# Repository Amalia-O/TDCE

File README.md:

# TDCE
FIUBA - Electrónica - Taller de Diseño de Circuitos Electrónicos - Trabajo Integrador

idealmente : RD2 = 1093 ohm RC1 RC2 deben ser iguales entre entre {100 y 1k} ohm. Admiten una dispersion de 10%. RE = 1.5k, A RC iguales tiende a desequilibrar el circuito cuando aumenta en valor. Es preferible que RE sea menor en vez de mayor. A RC2 > RC1 : punto de reposo en 4.97 y siguie siendo mejor que RE sea mejor a que sea mayor A RC1 > RC2 : Punto de reposo en 5v! conviene mucho mas que RE sea mas chica

Eficiencia:
  75.5 - 71.2 : En Re = 1.5k y par diferencial no darlington. Regulacion de linea es -2e-5. Regulacion de carga es 4e-5. Corriente por Re 0.65 mA.En este caso hay mayor RRMC que con RE= 1k.
  75.5 - 71.2 : En Re = 1.0k y par diferencial no darlington. Regulacion de linea es -2e-5. Regulacion de carga es 4e-5. Corriente por Re \simeq 1mA. Ganancia de lazo 80dB. lazo cerrado es de 98dB
  75.5 - 71.2 : En Re = 1.5K y par diferencial darlington. Regulacion de linea es de 9e-5. Regulacion de carga es 0.0002. Corriente por Re \simeq 0.4mA
  75.4 - 71.4 : En Re = 500 y par diferencial darlington. Regulacion de linea es 2.75e-5. Regulacion de carga es 9.95e-5. Corriente por Re \simeq 1mA

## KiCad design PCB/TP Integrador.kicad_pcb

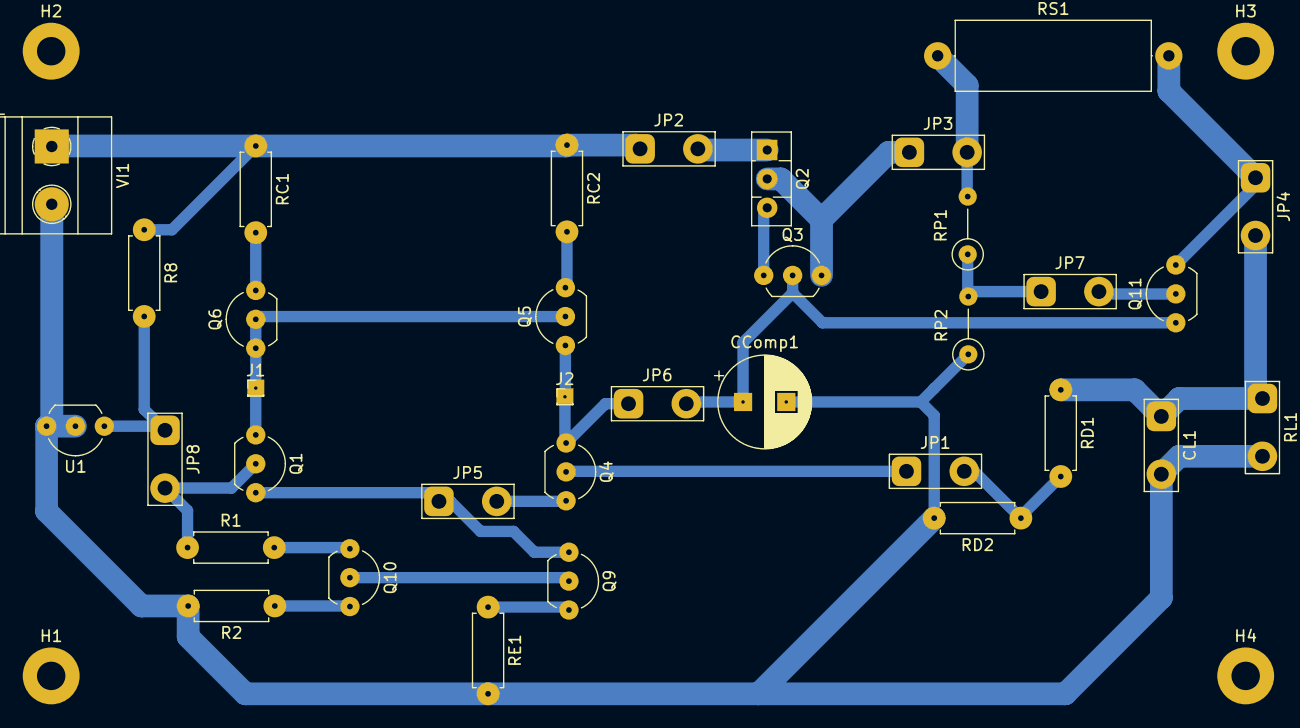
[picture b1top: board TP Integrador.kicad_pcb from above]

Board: 2 copper layers, 39 parts (0 on the bottom side), 24 nets.

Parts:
CComp1: 12n; CP_Radial_D8.0mm_P3.80mm
CL1: Jumper_2_Bridged; TestPoint_2Pads_Pitch5.08mm_Drill1.3mm
H1, H2, H3, H4: MountingHole; MountingHole_2.5mm_Pad
J1, J2: Conn_01x01_Pin; PinHeader_1x01_P1.00mm_Vertical
JP1, JP2, JP3, JP4, JP5, JP6, JP7, JP8: Jumper_2_Bridged; TestPoint_2Pads_Pitch5.08mm_Drill1.3mm
Q1, Q4, Q9, Q10, Q11: BC547C; TO-92_Inline_Wide
Q2: 2SB631; TO-126-3_Vertical
Q3: BC547; TO-92_Inline_Wide
Q5, Q6: BC557C; TO-92_Inline_Wide
R1: 1.5k; R_Axial_DIN0207_L6.3mm_D2.5mm_P7.62mm_Horizontal
R2: 390; R_Axial_DIN0207_L6.3mm_D2.5mm_P7.62mm_Horizontal
R8: 2200; R_Axial_DIN0207_L6.3mm_D2.5mm_P7.62mm_Horizontal
RC1, RC2: 510; R_Axial_DIN0207_L6.3mm_D2.5mm_P7.62mm_Horizontal
RD1, RD2: 1k; R_Axial_DIN0207_L6.3mm_D2.5mm_P7.62mm_Horizontal
RE1: 390; R_Axial_DIN0207_L6.3mm_D2.5mm_P7.62mm_Horizontal
RL1: Jumper_2_Bridged; TestPoint_2Pads_Pitch5.08mm_Drill1.3mm
RP1, RP2: 50; R_Axial_DIN0207_L6.3mm_D2.5mm_P5.08mm_Vertical
RS1: 2.2; R_Axial_DIN0617_L17.0mm_D6.0mm_P20.32mm_Horizontal
U1: TL431D; TO-92_Inline_Wide
VI1: 6.8; TerminalBlock_Phoenix_MKDS-1,5-2-5.08_1x02_P5.08mm_Horizont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

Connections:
GND: CComp1.2, CL1.2 (B), R2.2, RD2.2, RE1.2, RL1.2 (B), RP2.1, U1.2 (A), U1.3 (A), VI1.2 (-)
unnamed: J1.e (Pin_1), Q1.1 (C), Q5.2 (B), Q6.1 (C), Q6.2 (B)
unnamed: J2.1, JP6.1 (A), Q4.1 (C), Q5.1 (C)
unnamed: JP1.1 (A), Q4.2 (B)
unnamed: JP1.2 (B), RD1.2, RD2.1
unnamed: JP2.2 (B), Q2.1 (E)
unnamed: JP3.1 (A), Q2.2 (C), Q3.3 (E)
unnamed: JP3.2 (B), RP1.2, RS1.1
unnamed: JP4.1 (A), Q11.3 (E), RS1.2
unnamed: JP5.1 (A), Q1.3 (E), Q9.1 (C)
unnamed: JP5.2 (B), Q4.3 (E)
unnamed: CComp1.1, JP6.2 (B), Q3.2 (B), Q11.1 (C)
unnamed: JP7.1 (A), RP1.1, RP2.2
unnamed: JP7.2 (B), Q11.2 (B)
unnamed: JP8.1 (A), R8.2, U1.1 (K)
unnamed: JP8.2 (B), Q1.2 (B), R1.1
unnamed: Q2.3 (B), Q3.1 (C)
unnamed: Q5.3 (E), RC2.2
unnamed: Q6.3 (E), RC1.2
unnamed: Q9.3 (E), RE1.1
unnamed: Q9.2 (B), Q10.1 (C), Q10.2 (B), R1.2
unnamed: Q10.3 (E), R2.1
vi: JP2.1 (A), R8.1, RC1.1, RC2.1, VI1.1 (+)
vo: CL1.1 (A), JP4.2 (B), RD1.1, RL1.1 (A)

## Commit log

2025-03-26 First Commit
    Regulador de Tension con 3 digitos de presición
2025-03-27 Agregando version 1
2025-03-27 Version 2
2025-03-27 Version 3
2025-03-27 Version 4
2025-03-27 Version 5 fallida
2025-03-27 Version 6 fallida
2025-03-27 Version 7
2025-03-27 Agregando version ami tuneada
2025-03-28 Versión posilble final
    Muy buen nombre
2025-03-28 Limitador de corriente
    Con divisor resistivo
    FALBAK
2025-03-28 Version 8
2025-03-29 Cambiando a transistores comerciales
2025-03-29 Avanzando con el limitador de corriente
2025-03-30 Add PCB
2025-03-30 Actualizando a las nuevas especificaciones
2025-03-31 Agregando labels y valores de prueba para el dividor en el limitador de corriente
2025-04-01 Poniendo lindo el circuito para poder medir todo
    Agregando el calculo de minima y maxima eficiencia
    Agregando el calculo del dropout
    Separando el realimentador de corriente, del limitador, preparando para el lazo de corriente
2025-04-01 Haciendolo lindo
2025-04-01 Version 1 del lazo de corriente
2025-04-01 Version 2 de lazo de corriente
2025-04-01 Agregando llave de seleccion temporal
2025-04-01 Correcciones de valores del lazo de corriente y limitador de corriente
2025-04-01 Agregando seccion de modelos
2025-04-02 Esquematico de LTSpice terminado para el checkpoint 1
2025-04-04 Upate PCB
2025-04-11 Actualizando a fin de checkpoint 1
2025-04-14 Llevando Icc al valor deseado
2025-04-14 Limpiando cosas
2025-04-14 Avanzando con la tensión de referencia
2025-04-15 Agregando el inicio de la compensasión
2025-04-15 Actualizando los transistores que estaban mal
    Los del espejo de corriente como carga activa
2025-04-22 Compensacion y eliminando carpeta tuneada
2025-04-22 moviendo a una carpeta de esquematico
2025-04-22 Agregando carpeta de checkpoints
2025-04-22 La cague con el readme
2025-04-23 Agregando el calculo de margen de fase y ganancia
2025-04-24 compensado
2025-04-24 Update checkpoint 2
2025-04-26 Terminando el checkpoint 2
2025-04-27 Edit Checkpoint 2
2025-04-29 Falta el disipador!!!
2025-04-29 Edit Rs, no falta el disipador!!
2025-04-30 Edit pads para que sean mas gorditos
2025-05-23 Agregando script para el nucleo
2025-05-25 Actualizando el algoritmo de seleccion del metodo de Erickson
2025-05-28 Agregando un reedme para ayudar con el uso del ejecutable
2025-05-28 Modificando el script para obtener más información de sus parámetros
2025-05-28 Obteniendo resultados para el caso medio y extremos
2025-06-12 Manejando mejor los scripts
2025-06-12 Agregando el checkpoint 4
2025-06-14 Agregando la etapa conmutada con el pwm, el bulk y el gate driver
2025-06-22 Agregando el generador de tension para alimentar el pwm y el gate driver
2025-06-22 Agregando el script correcto del metodo de erickson
2025-06-23 Agregando la parte de realimentación
2025-06-23 Circuito completo
2025-06-23 mejorando la realimentación
2025-06-24 Ultimos cambios al diseño
2025-06-24 Cambiando los 12n en 15n
